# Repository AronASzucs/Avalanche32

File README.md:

# Avalanche32: ESP32-S3 Geiger Counter

A handheld, battery-powered Geiger counter built around the **ESP32-S3-WROOM-1** and a Soviet **SBM-20** Geiger–Müller tube. It has a firmware-regulated 400 V supply, an audible click for each count, a 2.42" OLED display, and a single USB-C port for both charging and programming.

> **Status: Rev A, in progress.** The perfboard prototype is working: it regulates the tube supply at 370–400 V, counts background radiation, and clearly detects real radioactive sources (see [Measurements](#measurements)). The Rev A schematic and PCB layout are complete, and the boards and parts have been ordered. Assembly and testing are next.

| Front | Back |
|---|---|
|  |  |

## Hardware Overview

| Block | Implementation |
|---|---|
| MCU | ESP32-S3-WROOM-1, native USB (no USB-UART bridge), BOOT and RESET buttons |
| Battery | 2S Li-ion / LiPo pack (7.4 V nominal, 6.0–8.4 V) on a JST-XH connector |
| Charger | TI BQ25886 2-cell boost charger with power-path management, charge-status and power-good LEDs |
| USB-C | 5 V input (5.1 kΩ CC pull-downs, no USB PD), 3 A polyfuse on VBUS, USBLC6-2 ESD protection on the data lines |
| Power switch | Slide switch driving an AO3401A P-FET load switch. The charger stays active, so the pack charges with the unit switched off. |
| 3.3 V rail | Diodes AP63203 synchronous buck converter |
| High voltage | Firmware-regulated boost from the system rail to ~400 V (details below) |
| Detection | SBM-20 cathode pulse → MMBT3904 pulse shaper → ESP32 interrupt |
| Audio | Piezo transducer switched by a 2N7002 low-side MOSFET, one click per count |
| Display | 2.42" 128×64 SSD1309 OLED module over SPI |
| Battery monitor | 1 MΩ / 330 kΩ divider into an ESP32 ADC input |

### High-Voltage Supply

- **Topology:** discontinuous-mode boost converter. The ESP32 drives a UCC27517 gate driver, which switches an STN1HNK60 600 V MOSFET into a 10 mH inductor, with a US1M fast-recovery rectifier.
- **Regulation:** closed-loop hysteretic control. A 3 × 100 MΩ + 680 kΩ divider (with a 2.2 nF filter cap) feeds the ESP32 ADC, and the firmware gates the boost pulses to hold the setpoint.
- **Protection:** a 450 V Zener clamp (3 × 150 V in series) on the output, plus a firmware overvoltage shutdown.
- **Filtering:** a 20 nF / 1 kV reservoir, then a 1 MΩ / 10 nF RC ripple filter, then a 5.1 MΩ anode resistor into the tube.
- **Layout:** the HV section sits in its own isolated area with a "400V High Voltage" marking on the silkscreen.

### GPIO Map (Rev A PCB)

| Signal | ESP32-S3 GPIO |
|---|---|
| HV_PWM (gate driver input) | IO4 |
| HV_SENSE (HV divider, ADC1) | IO2 |
| PULSE (tube pulse, active low) | IO5 |
| PIEZO | IO6 |
| VBAT_SENSE (ADC1) | IO1 |
| OLED SCK / MOSI / CS / DC / RST | IO12 / IO11 / IO10 / IO13 / IO21 |
| USB D− / D+ | IO19 / IO20 |

Test points are provided for 3.3 V, GND, PULSE and HV_SENSE.

### PCB

| Parameter | Value |
|---|---|
| Dimensions | 137 × 84 mm |
| Layers | 2 (1.6 mm FR-4, 1 oz copper) |
| Finish | Black solder mask, white silkscreen, HASL |
| Mounting | 4 × M3 mounting holes |

## Measurements

These readings are from the perfboard prototype, with each sample placed directly against the SBM-20 tube. Dose rates use the firmware's conversion factor of 0.0057 µSv/h per CPM (SBM-20, Cs-137 basis), so they are indicative only.

| Source | CPM | × Background | Indicated µSv/h |
|---|---|---|---|
| Normal indoor background | 15–25 | 1× | ~0.09–0.14 |
| Uranium glass plate | 300–400 | ~17× | ~1.7–2.3 |
| Vintage radium-dial watch | 350–450 | ~20× | ~2.0–2.6 |
| Watch + plate together | 550–650 | ~30× | ~3.1–3.7 |
| Fiestaware red-orange saucer (uranium glaze) | ~8,700 | ~435× | ~50 |
| Fiestaware cup resting on saucer | ~13,400 | ~670× | ~76 |

Contact readings on glazed ceramics are mostly beta from the uranium decay chain, so the µSv/h values overstate the actual dose.

## Known Issue: Tube Re-Firing

The current SBM-20 is degraded and sometimes fires a burst of 100–1000+ pulses instead of a single one. The firmware works around this with a burst filter (`BURST_FILTER`) that merges each burst into one count, at the cost of undercounting at very high rates. A replacement tube is on the way.

## Firmware

`Firmware/HV_Test/HV_Test.ino` is a bench test for the HV supply and counting chain, written for the Arduino ESP32 core. It provides:

- Hysteretic HV regulation (370 V setpoint, 5 V hysteresis) with a 460 V overvoltage shutdown.
- An interrupt-driven pulse counter with the optional burst filter (2.5 ms window).
- A 60-second rolling CPM and an estimated µSv/h.
- A 4 kHz piezo click for each count.
- Serial output at 115200 baud showing HV, boost on-time, total and raw counts, CPM and µSv/h. To change the boost on-time, send a number from 5 to 120 (µs).

> **Note:** this sketch targets the perfboard prototype, which uses a classic ESP32 dev board. Its pin assignments (IO4, IO35, IO27, IO25) do **not** match the Rev A PCB. Update the constants at the top of the file using the [GPIO map](#gpio-map-rev-a-pcb) before running it on the PCB.

## Repository Layout

| Path | Contents |
|---|---|
| `ESP32-Geiger-Counter.kicad_*` | KiCad project: schematic, PCB and design rules |
| `Custom Parts.kicad_sym`, `libs/` | Custom symbols, footprints and 3D models |
| `production/` | JLCPCB fabrication outputs: Gerber/drill archive, BOM, pick-and-place and IPC netlist |
| `bom/ibom.html` | Interactive BOM for hand assembly |
| `Images/` | 3D renders (`3D/`) and per-layer plots (`Layers/`) |
| `scripts/generate_images.py` | Regenerates everything in `Images/` using `kicad-cli` |
| `Firmware/` | ESP32 firmware |
| `Draft1.asc` | LTspice simulation of the HV boost |

To regenerate the images (requires KiCad 9+ and, for PNG layer plots, `pip install pymupdf`):

```sh
python scripts/generate_images.py
```

## Roadmap

- [x] HV boost designed and simulated in LTspice
- [x] Perfboard HV prototype with regulation verified at 370–400 V
- [x] SBM-20 background count test (15–25 CPM indoors)
- [x] Source tests: uranium glass, radium-dial watch and uranium-glazed Fiestaware detected (up to ~670× background)
- [x] Bench-test firmware: hysteretic HV control, rolling CPM, µSv/h estimate, piezo click
- [x] Full schematic: power, charger, ESP32-S3, HV supply, detector and display
- [x] Rev A PCB layout and fabrication outputs
- [x] Rev A boards and parts ordered
- [ ] Rev A assembly and bring-up
- [ ] Application firmware: OLED UI, menus, dose alarm, logging, battery monitoring

## Tools

KiCad · LTspice · Arduino (ESP32 core) · C++

## Safety

This device generates **~400 V DC**. The stored energy is small, but do not touch the HV section while the unit is powered. Before handling the board, let the capacitors discharge: wait for the HV reading to fall to 0 V.

Store radioactive test samples (radium dials, uranium glass, uranium-glazed ceramics) sealed and away from living spaces. Never open radium-dial watches or gauges, and never eat or drink from uranium-glazed dishware.

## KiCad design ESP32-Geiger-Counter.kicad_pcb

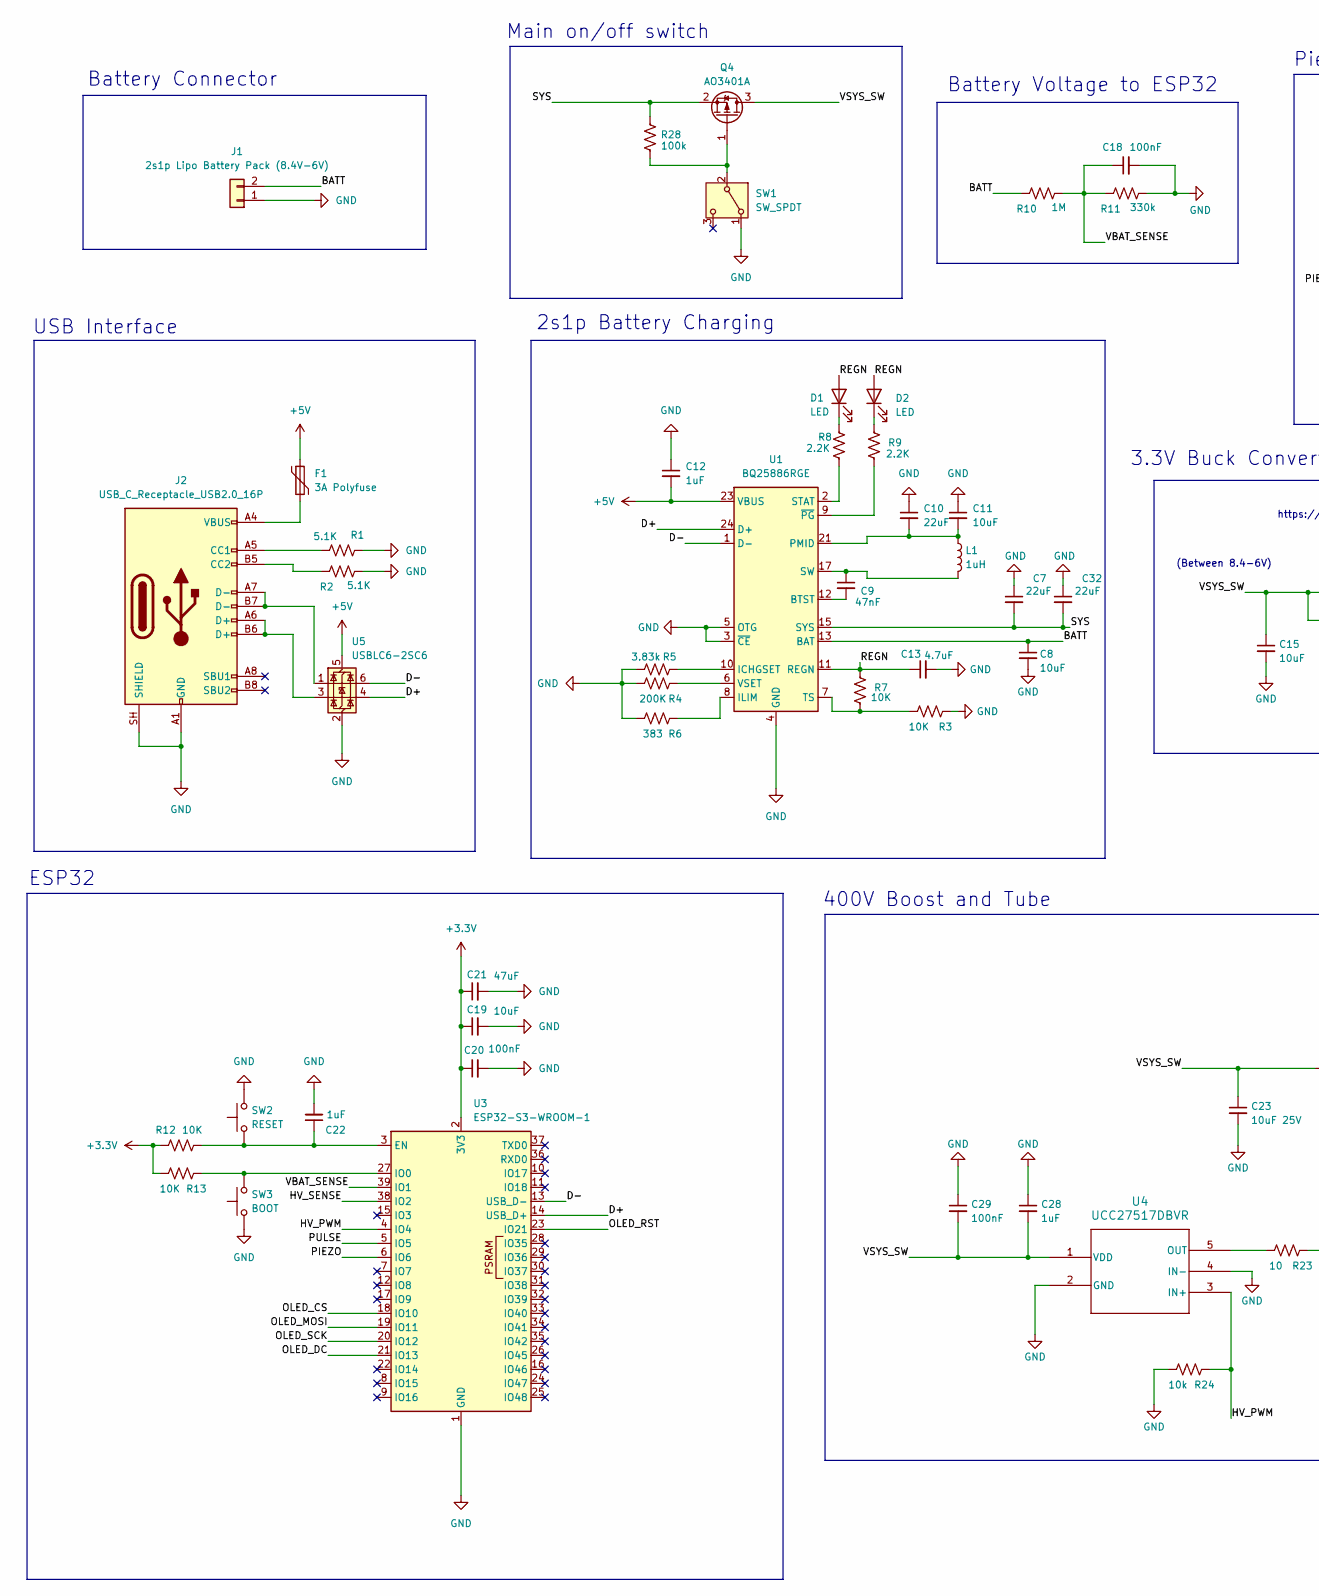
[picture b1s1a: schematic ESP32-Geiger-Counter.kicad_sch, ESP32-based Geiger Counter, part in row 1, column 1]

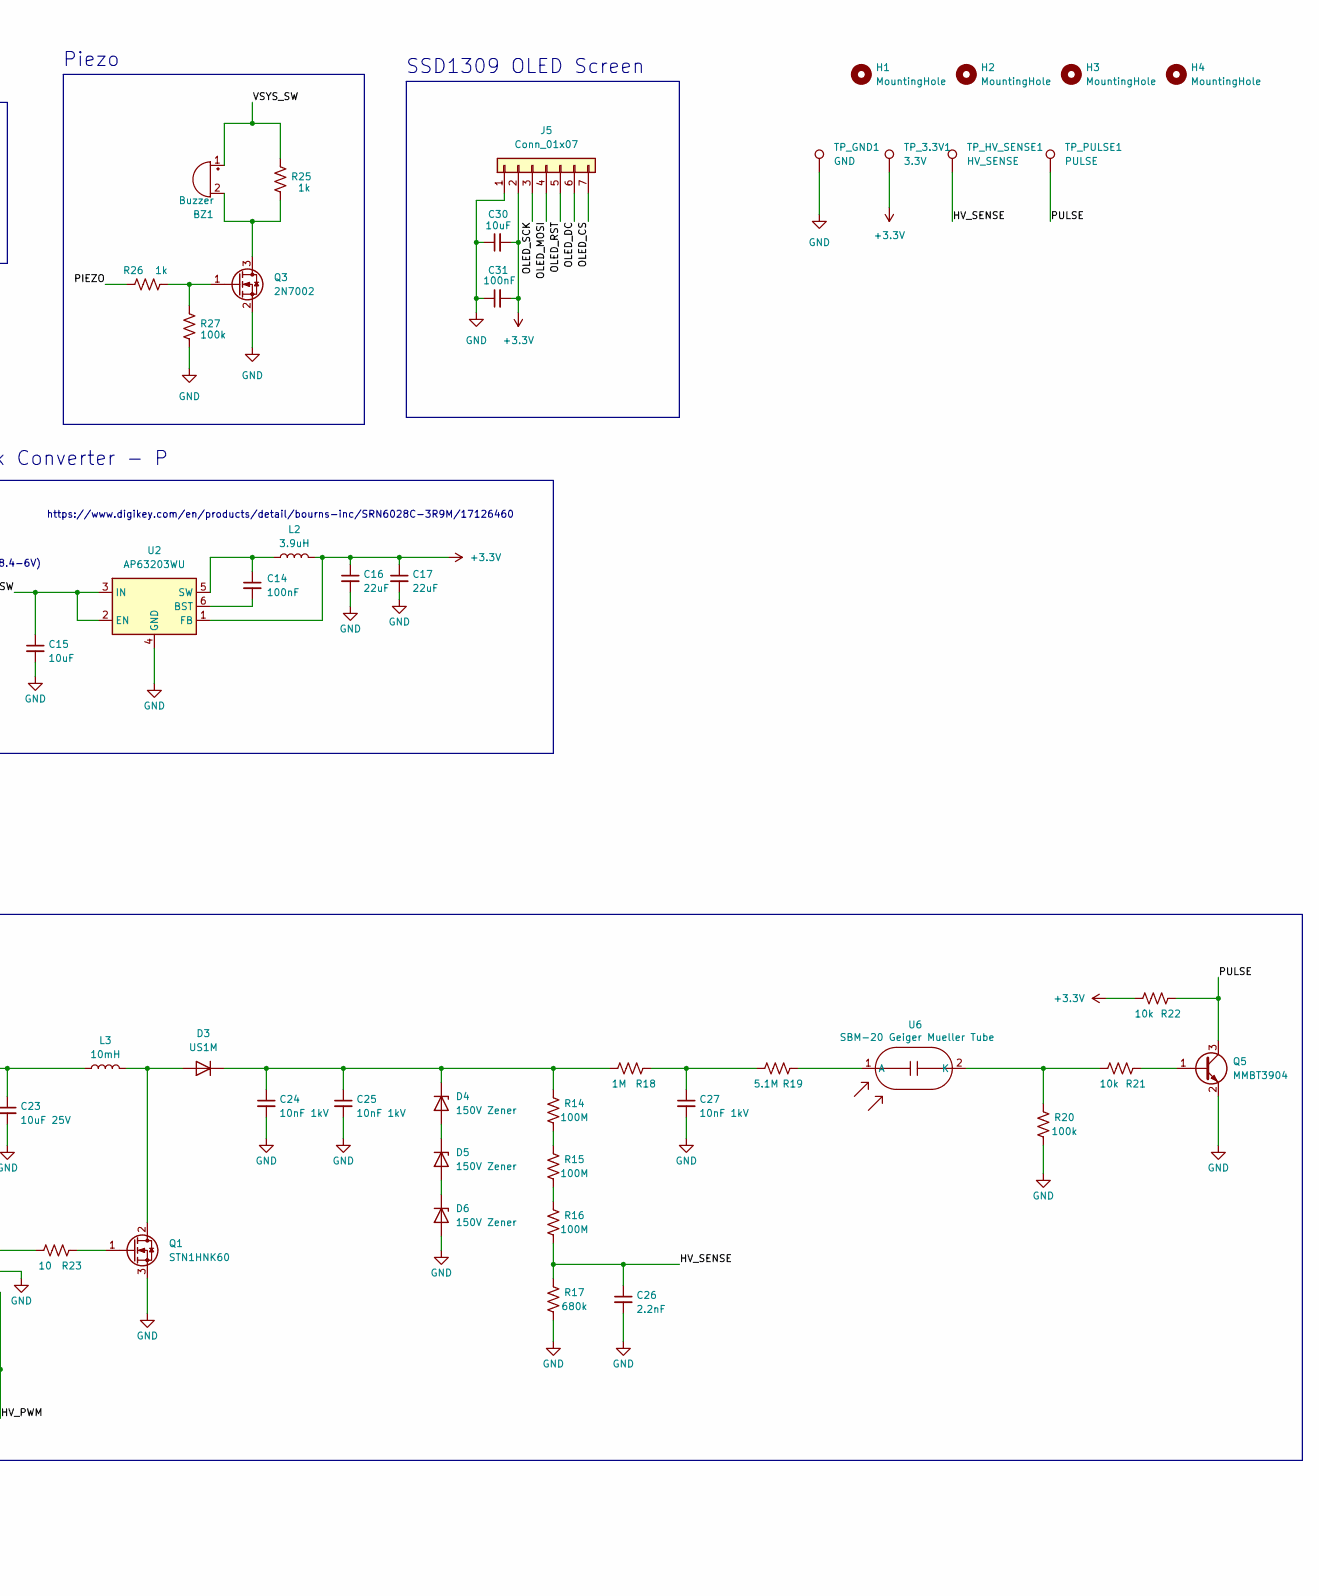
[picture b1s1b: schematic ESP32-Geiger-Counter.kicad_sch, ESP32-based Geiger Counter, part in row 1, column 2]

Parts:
BZ1: Buzzer; XDCR_CPT-1203-78-SMT-TR
C7, C10, C16, C17, C32: 22uF; C_1206_3216Metric
C8, C11, C15, C19, C30: 10uF; C_1206_3216Metric
C9: 47nF; C_0805_2012Metric
C12, C22, C28: 1uF; C_0805_2012Metric
C13: 4.7uF; C_0805_2012Metric
C14, C18, C20, C29, C31: 100nF; C_0805_2012Metric
C21: 47uF; C_1206_3216Metric
C23: 10uF 25V; C_1206_3216Metric
C24, C25, C27: 10nF 1kV; C_1206_3216Metric
C26: 2.2nF; C_0805_2012Metric
D1, D2: LED; LED_0805_2012Metric
D3: US1M; D_SMA
D4, D5, D6: 150V Zener; D_SMA
F1: 3A Polyfuse; Fuse_2920_7451Metric
H1, H2, H3, H4: MountingHole; MountingHole_3.2mm_M3
J1: 2s1p Lipo Battery Pack (8.4V-6V); JST_XH_S2B-XH-A_1x02_P2.50mm_Horizontal
J2: USB_C_Receptacle_USB2.0_16P; USB_C_Receptacle_GCT_USB4105-xx-A_16P_TopMnt_Horizontal
J5: Conn_01x07; OLED_2.42in_SSD1309_SPI_7pin
L1: 1uH; IND_SRP4020TA-1R0M
L2: 3.9uH; L_Bourns-SRN6028
L3: 10mH; L_Radial_D12.5mm_P7.00mm_Fastron_09HCP
Q1: STN1HNK60; SOT-223-3_TabPin2
Q3: 2N7002; SOT-23
Q4: AO3401A; SOT-23
Q5: MMBT3904; SOT-23
R1, R2: 5.1K; R_0805_2012Metric
R3, R7, R12, R13: 10K; R_0805_2012Metric
R4: 200K; R_0805_2012Metric
R5: 3.83k; R_0805_2012Metric
R6: 383; R_0805_2012Metric
R8, R9: 2.2K; R_0805_2012Metric
R10: 1M; R_0805_2012Metric
R11: 330k; R_0805_2012Metric
R14, R15, R16: 100M; R_1206_3216Metric
R17: 680k; R_0805_2012Metric
R18: 1M; R_1206_3216Metric
R19: 5.1M; R_1206_3216Metric
R20, R27, R28: 100k; R_0805_2012Metric
R21, R22, R24: 10k; R_0805_2012Metric
R23: 10; R_0805_2012Metric
R25, R26: 1k; R_0805_2012Metric
SW1: SW_SPDT; SW_Slide_SPDT_Angled_CK_OS102011MA1Q
SW2: RESET; SW_PUSH_6mm
SW3: BOOT; SW_PUSH_6mm
TP_3.3V1: 3.3V; TestPoint_Keystone_5015_Micro_Mini
TP_GND1: GND; TestPoint_Keystone_5015_Micro_Mini
TP_HV_SENSE1: HV_SENSE; TestPoint_Keystone_5015_Micro_Mini
TP_PULSE1: PULSE; TestPoint_Keystone_5015_Micro_Mini
U1: BQ25886RGE; Texas_RGE0024H_VQFN-24-1EP_4x4mm_P0.5mm_EP2.7x2.7mm_Thermal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
U2: AP63203WU; TSOT-23-6
U3: ESP32-S3-WROOM-1
U4: UCC27517DBVR; DBV5_TEX
U5: USBLC6-2SC6; SOT-23-6
U6: SBM-20 Geiger Mueller Tube; SBM-20 Tube

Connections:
+3.3V: C16.1, C17.1, C19.1, C20.1, C21.1, C30.2, C31.2, J5.2, L2.2, R12.2, R13.1, R22.1, TP_3.3V1.1, U2.1 (FB), U3.2 (3V3); also elsewhere on the board
+5V: C12.2, F1.1, U1.23 (VBUS), U5.5 (VBUS)
/BATT: C8.1, J1.2, R10.2, U1.13 (BAT), U1.14 (BAT)
/D+: U1.24 (D+), U3.14 (USB_D+), U5.4 (I/O2)
/D-: U1.1 (D-), U3.13 (USB_D-), U5.6 (I/O1)
/HV_PWM: R24.2, U3.4 (IO4), U4.3 (IN+)
/HV_SENSE: C26.1, R16.1, R17.2, TP_HV_SENSE1.1, U3.38 (IO2); also elsewhere on the board
/OLED_CS: J5.7, U3.18 (IO10)
/OLED_DC: J5.6, U3.21 (IO13)
/OLED_MOSI: J5.4, U3.19 (IO11)
/OLED_RST: J5.5, U3.23 (IO21)
/OLED_SCK: J5.3, U3.20 (IO12)
/PIEZO: R26.2, U3.6 (IO6)
/PULSE: Q5.3 (C), R22.2, TP_PULSE1.1, U3.5 (IO5); also elsewhere on the board
/REGN: C13.1, D1.2 (A), D2.2 (A), R7.2, U1.11 (REGN)
/SYS: C7.2, C32.2, Q4.2 (S), R28.2, U1.15 (SYS), U1.16 (SYS)
/VBAT_SENSE: C18.1, R10.1, R11.2, U3.39 (IO1)
/VSYS_SW: BZ1.1 (+), C15.1, C23.1, C28.2, C29.2, L3.1, Q4.3 (D), R25.2, U2.2 (EN), U2.3 (IN), U4.1 (VDD)
GND: C7.1, C8.2, C10.1, C11.1, C12.1, C13.2, C15.2, C16.2, C17.2, C18.2, C19.2, C20.2, C21.2, C22.2, C23.2, C24.2, C25.2, C26.2, C27.2, C28.1, C29.1, C30.1, C31.1, C32.1, D6.2 (A), J1.1, J2.A1 (GND), J2.A12 (GND), J2.B1 (GND), J2.B12 (GND), J2.SH (SHIELD), J5.1, Q1.3 (S), Q3.2 (S), Q5.2 (E), R1.2, R2.1, R3.2, R4.1, R5.2, R6.1, R11.1, R17.1, R20.1, R24.1, R27.1, SW1.1 (A), SW2.2, SW3.1, TP_GND1.1, U1.3 (~CE), U1.4 (GND), U1.5 (OTG), U1.19 (GND), U1.20 (GND), U1.25 (GND), U2.4 (GND), U3.1 (GND), U3.40 (GND), U3.41 (GND), U4.2 (GND), U4.4 (IN-), U5.2 (GND); also elsewhere on the board
unnamed: BZ1.2 (-), Q3.3 (D), R25.1
unnamed: C9.1, L1.2, U1.17 (SW), U1.18 (SW)
unnamed: C10.2, C11.2, L1.1, U1.21 (PMID), U1.22 (PMID)
unnamed: C27.1, R18.2, R19.1
unnamed: D1.1 (K), R8.2
unnamed: D2.1 (K), R9.2
unnamed: D3.2 (A), L3.2, Q1.2 (D)
unnamed: C24.1, C25.1, D3.1 (K), D4.1 (K), R14.2, R18.1
unnamed: D4.2 (A), D5.1 (K)
unnamed: D5.2 (A), D6.1 (K)
unnamed: F1.2, J2.A4 (VBUS), J2.A9 (VBUS), J2.B4 (VBUS), J2.B9 (VBUS)
unnamed: J2.A5 (CC1), R1.1
unnamed: J2.B5 (CC2), R2.2
unnamed: J2.A6 (D+), J2.B6 (D+), U5.3 (I/O2)
unnamed: J2.A7 (D-), J2.B7 (D-), U5.1 (I/O1)
unnamed: Q1.1 (G), R23.2
unnamed: Q3.1 (G), R26.1, R27.2
unnamed: Q4.1 (G), R28.1, SW1.2 (B)
unnamed: Q5.1 (B), R21.2
unnamed: R14.1, R15.2
unnamed: R15.1, R16.2
unnamed: C9.2, U1.12 (BTST)
unnamed: R5.1, U1.10 (ICHGSET)
unnamed: R6.2, U1.8 (ILIM)
unnamed: R8.1, U1.2 (STAT)
unnamed: R3.1, R7.1, U1.7 (TS)
unnamed: R4.2, U1.6 (VSET)
unnamed: R9.1, U1.9 (~PG)
unnamed: C14.2, U2.6 (BST)
unnamed: C14.1, L2.1, U2.5 (SW)
unnamed 49: C22.1, R12.1, SW2.1, U3.3 (EN); also elsewhere on the board
unnamed 50: R13.2, SW3.2, U3.27 (IO0); also elsewhere on the board
unnamed: R23.1, U4.5 (OUT)
unnamed: R19.2, U6.1 (A)
unnamed: R20.2, R21.1, U6.2 (K)

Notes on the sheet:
2s1p Battery Charging
ESP32
Main on/off switch
Battery Voltage to ESP32
USB Interface
(Between 8.4-6V)
Piezo
https://www.digikey.com/en/products/detail/bourns-inc/SRN6028C-3R9M/17126460
Battery Connector
SSD1309 OLED Screen
400V Boost and Tube
3.3V Buck Converter - P

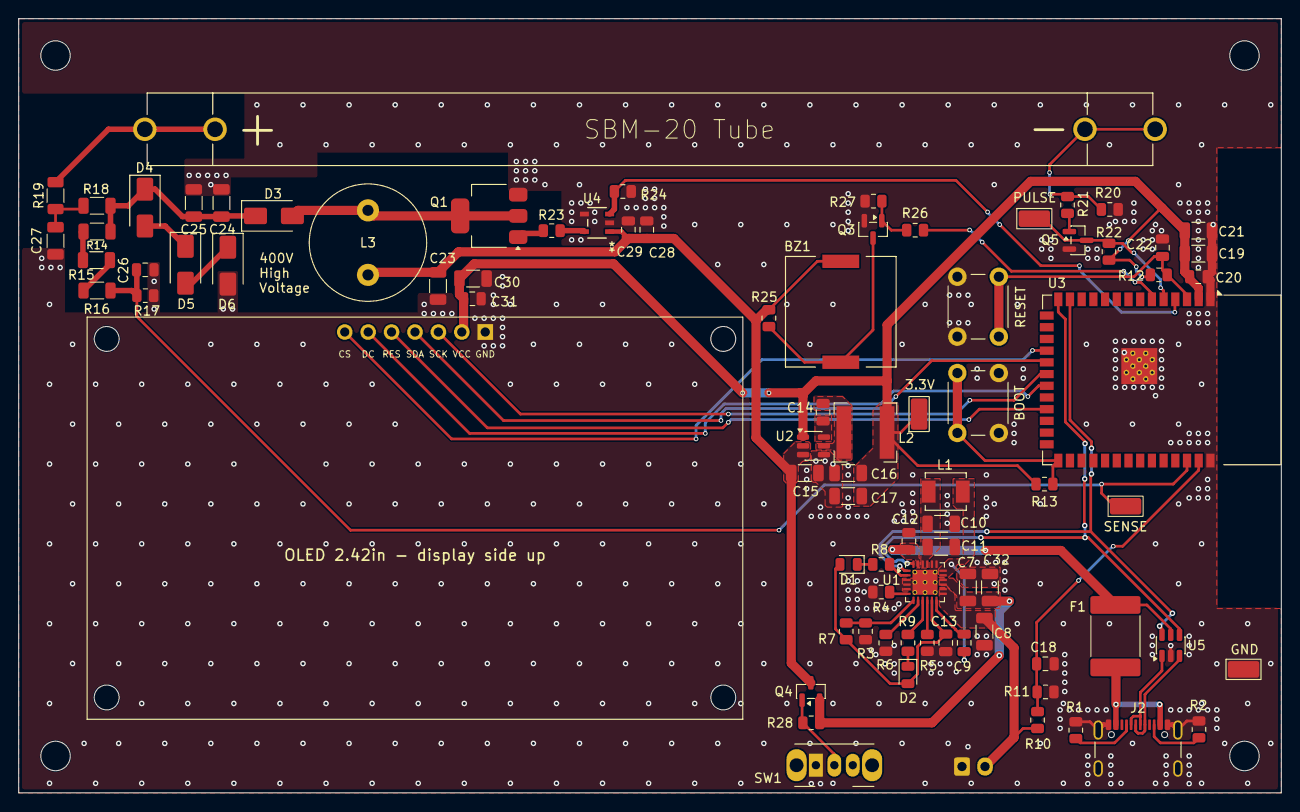
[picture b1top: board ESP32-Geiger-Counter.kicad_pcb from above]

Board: 2 copper layers, 137.0 x 84.0 mm, 89 parts (1 on the bottom side), 54 nets.

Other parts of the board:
3.3V: 3.3V; TestPoint_Keystone_5015_Micro_Mini
BOOT: BOOT; SW_PUSH_6mm
GND: GND; TestPoint_Keystone_5015_Micro_Mini
PULSE: PULSE; TestPoint_Keystone_5015_Micro_Mini
RESET: RESET; SW_PUSH_6mm
SENSE: HV_SENSE; TestPoint_Keystone_5015_Micro_Mini

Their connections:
+3.3V: 3.3V.1 (1_1); also elsewhere on the board
/HV_SENSE: SENSE.1 (1_1); also elsewhere on the board
/PULSE: PULSE.1 (1_1); also elsewhere on the board
GND: BOOT.1, GND.1 (1_1), RESET.2; also elsewhere on the board
unnamed 49: RESET.1; also elsewhere on the board
unnamed 50: BOOT.2; also elsewhere on the board

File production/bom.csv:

Designator,Footprint,Quantity,Value,LCSC Part #
3.3V,TestPoint_Keystone_5015_Micro_Mini,1,3.3V,
BOOT,SW_PUSH_6mm,1,BOOT,
BZ1,XDCR_CPT-1203-78-SMT-TR,1,Buzzer,
"C10, C16, C17, C32, C7",1206,5,22uF,
"C11, C15, C19, C30, C8",1206,5,10uF,
"C12, C22, C28",0805,3,1uF,
C13,0805,1,4.7uF,
"C14, C18, C20, C29, C31",0805,5,100nF,
C21,1206,1,47uF,
C23,1206,1,10uF 25V,
"C24, C25, C27",1206,3,10nF 1kV,
C26,0805,1,2.2nF,
C9,0805,1,47nF,
"D1, D2",0805,2,LED,
D3,D_SMA,1,US1M,
"D4, D5, D6",D_SMA,3,150V Zener,
F1,2920,1,3A Polyfuse,
GND,TestPoint_Keystone_5015_Micro_Mini,1,GND,
J1,JST_XH_S2B-XH-A_1x02_P2.50mm_Horizontal,1,2s1p Lipo Battery Pack (8.4V-6V),
J2,USB_C_Receptacle_GCT_USB4105-xx-A_16P_TopMnt_Horizontal,1,USB_C_Receptacle_USB2.0_16P,
J5,OLED_2.42in_SSD1309_SPI_7pin,1,Conn_01x07,
L1,IND_SRP4020TA-1R0M,1,1uH,
L2,L_Bourns-SRN6028,1,3.9uH,
L3,L_Radial_D12.5mm_P7.00mm_Fastron_09HCP,1,10mH,
PULSE,TestPoint_Keystone_5015_Micro_Mini,1,PULSE,
Q1,SOT-223-3_TabPin2,1,STN1HNK60,
Q3,SOT-23,1,2N7002,
Q4,SOT-23,1,AO3401A,
Q5,SOT-23,1,MMBT3904,
"R1, R2",0805,2,5.1K,
R10,0805,1,1M,
R11,0805,1,330k,
"R12, R13, R21, R22, R24, R3, R7",0805,7,10K,
"R14, R15, R16",1206,3,100M,
R17,0805,1,680k,
R18,1206,1,1M,
R19,1206,1,5.1M,
"R20, R27, R28",0805,3,100k,
R23,0805,1,10,
"R25, R26",0805,2,1k,
R4,0805,1,200K,
R5,0805,1,3.83k,
R6,0805,1,383,
"R8, R9",0805,2,2.2K,
RESET,SW_PUSH_6mm,1,RESET,
SENSE,TestPoint_Keystone_5015_Micro_Mini,1,HV_SENSE,
SW1,SW_Slide_SPDT_Angled_CK_OS102011MA1Q,1,SW_SPDT,
U1,Texas_RGE0024H_VQFN-24-1EP_4x4mm_P0.5mm_EP2.7x2.7mm_ThermalVias,1,BQ25886RGE,
U2,TSOT-23-6,1,AP63203WU,
U3,ESP32-S3-WROOM-1,1,ESP32-S3-WROOM-1,
U4,DBV5_TEX,1,UCC27517DBVR,
U5,SOT-23-6,1,USBLC6-2SC6,
U6,SBM-20 Tube,1,SBM-20 Geiger Mueller Tube,

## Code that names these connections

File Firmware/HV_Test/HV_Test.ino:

// Geiger counter HV bench test - ESP32 (Arduino core)
// Hysteretic boost control, pulse counting, rolling CPM, piezo click.
// Serial @ 115200. Send a number (5-120) to change the boost on-time in us.

// ---------------- Config ----------------
const int HV_PWM_PIN   = 4;    // -> gate driver input
const int HV_SENSE_PIN = 35;   // <- HV divider tap (must be an ADC1 pin)
const int PULSE_PIN    = 27;   // <- pulse shaper output (active low)
const int PIEZO_PIN    = 25;   // -> piezo

const float DIV_RATIO  = (300.0e6 + 680.0e3) / 680.0e3;   // HV = Vsense * ratio
const float HV_TARGET  = 370.0;
const float HV_HYST    = 5.0;
const float HV_ABS_MAX = 460.0;

const bool     BURST_FILTER = true;   // merge tube re-firing bursts into one count
const uint32_t BURST_GAP_US = 5000;   // quiet time required before a new count

const float USV_PER_CPM = 0.0057;     // SBM-20, Cs-137 basis

uint32_t onTimeUs = 60;
const uint32_t PERIOD_US = 500;

// ---------------- Counting ----------------
volatile uint32_t counts = 0;
volatile uint32_t rawPulses = 0;
volatile uint32_t lastPulseUs = 0;

void IRAM_ATTR onPulse() {
  uint32_t now = micros();
  rawPulses++;
  // Every pulse restarts the window, so a whole burst becomes one count.
  if (!BURST_FILTER || now - lastPulseUs > BURST_GAP_US) counts++;
  lastPulseUs = now;
}

uint32_t bucket[60] = {0};   // 60 x 1 s buckets for rolling CPM
uint8_t  bucketIdx = 0;
uint32_t lastBucketCount = 0, lastBucketMs = 0, secondsRun = 0;

float readHV() {
  uint32_t mv = 0;
  for (int i = 0; i < 8; i++) mv += analogReadMilliVolts(HV_SENSE_PIN);
  return (mv / 8.0f) / 1000.0f * DIV_RATIO;
}

void setup() {
  pinMode(HV_PWM_PIN, OUTPUT);
  digitalWrite(HV_PWM_PIN, LOW);
  Serial.begin(115200);
  analogSetPinAttenuation(HV_SENSE_PIN, ADC_2_5db);   // ~0-1.25 V input range
  pinMode(PULSE_PIN, INPUT_PULLUP);
  attachInterrupt(digitalPinToInterrupt(PULSE_PIN), onPulse, FALLING);
  delay(1000);
  Serial.printf("HV test start. Target %.0f V, burst filter %s.\n",
                HV_TARGET, BURST_FILTER ? "ON" : "OFF");
}

void loop() {
  static bool pulsing = true;
  static uint32_t lastPrint = 0;
  static uint32_t lastClicked = 0;

  float hv = readHV();

  if (hv > HV_ABS_MAX) {
    digitalWrite(HV_PWM_PIN, LOW);
    Serial.printf("OVERVOLTAGE %.0f V - halted. Reset to retry.\n", hv);
    while (true) delay(1000);
  }

  if (hv >= HV_TARGET) pulsing = false;
  else if (hv < HV_TARGET - HV_HYST) pulsing = true;

  if (pulsing) {
    digitalWrite(HV_PWM_PIN, HIGH);
    delayMicroseconds(onTimeUs);
    digitalWrite(HV_PWM_PIN, LOW);
    delayMicroseconds(PERIOD_US - onTimeUs);
  }

  if (Serial.available()) {
    long v = Serial.parseInt();
    if (v >= 5 && v <= 120) {
      onTimeUs = v;
      Serial.printf("on-time = %lu us\n", onTimeUs);
    }
  }

  if (millis() - lastBucketMs >= 1000) {
    lastBucketMs += 1000;
    uint32_t c = counts;
    bucket[bucketIdx] = c - lastBucketCount;
    lastBucketCount = c;
    bucketIdx = (bucketIdx + 1) % 60;
    if (secondsRun < 60) secondsRun++;
  }

  if (millis() - lastPrint > 1000) {
    lastPrint = millis();
    uint32_t sum = 0;
    for (int i = 0; i < 60; i++) sum += bucket[i];
    float cpm = secondsRun ? sum * 60.0f / secondsRun : 0;   // scaled until first minute fills
    Serial.printf("HV = %6.1f V  on=%lu us  total=%lu  raw=%lu  CPM=%5.1f%s  ~%.3f uSv/h\n",
                  hv, onTimeUs, counts, rawPulses, cpm,
                  secondsRun < 60 ? " (warming up)" : "", cpm * USV_PER_CPM);
  }

  if (counts != lastClicked) {
    lastClicked = counts;
    tone(PIEZO_PIN, 4000, 3);
  }
}
